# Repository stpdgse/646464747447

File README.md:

# Automated PCB toolchain

One script sets up a headless, scriptable PCB workflow on Ubuntu 24.04 (x86_64):

| Tool | Purpose |
|---|---|
| KiCad 9.0 (PCBNew, `kicad-cli`) | Board editor, DRC, Gerber/drill export, Python `pcbnew` API |
| SKiDl | Describe circuits in Python, emit KiCad netlists |
| Fabrication Toolkit (Benny Megidish) | JLCPCB-ready Gerber / BOM / CPL output |
| Freerouting | Headless autorouter (Specctra DSN in, SES out) |

## Install

```bash
sudo ./setup-eda.sh            # install everything, then run the smoke test
sudo ./setup-eda.sh --no-test  # install only
sudo ./setup-eda.sh --test     # smoke test only
```

The script is idempotent. Open a new shell afterwards (or `source /etc/profile.d/eda.sh`).

## Pipeline

```
SKiDl script ──► netlist ──► PCBNew (place, outline) ──► DSN ──► Freerouting ──► SES
                                                                                  │
                        JLCPCB files ◄── Fabrication Toolkit ◄── routed .kicad_pcb ◄┘
```

Route a board headless:

```bash
freerouting -de board.dsn -do board.ses --gui.enabled=false
```

## Gotchas this script already handles

- SKiDl defaults to KiCad 10 mode; scripts must call `set_default_tool(KICAD9)`.
- SKiDl needs `KICAD9_SYMBOL_DIR` and KiCad's global `fp-lib-table`, which KiCad only
  creates on first GUI launch. The script sets both up.
- SKiDl's dependencies fail to build with the distro's patched pip, so it lives in a venv
  (`/opt/eda/venv`) on the system Python 3.12, which is the interpreter `pcbnew` is built for.
- Freerouting 2.4.1 needs Java 25; the default Java 21 fails with `UnsupportedClassVersionError`.
- The Fabrication Toolkit download is verified against the SHA-256 published in KiCad's
  plugin index before it is installed.

## Game Boy Color-style handheld (practice board)

A beginner-solderable, all through-hole handheld: ESP32-S3-DevKitC-1 on the underside, a 2.8"
ILI9341 LCD, 8 buttons, an I2S amplifier module. Board v0.3 is 90 x 98 mm (inside JLCPCB's cheapest
size tier). Full requirements and every verified fact: `docs/gbc-handheld-spec.md`.
Build and soldering instructions: `gbc-handheld/ASSEMBLY.md`. Shopping list: `gbc-handheld/build/BOM.md`.

Rebuild everything from source (after `sudo ./setup-eda.sh`):

```bash
source /etc/profile.d/eda.sh
python3 gbc-handheld/schematic.py                                  # SKiDl -> netlist, ERC
python3 -I gbc-handheld/verify_netlist.py gbc-handheld/build/gbc_handheld.net
python3 gbc-handheld/build_board.py route                          # place, autoroute, fix thermals
python3 gbc-handheld/verify_board.py                               # board vs netlist, fab limits
kicad-cli pcb drc --severity-all --all-track-errors --output /tmp/drc.rpt gbc-handheld/build/gbc_handheld.kicad_pcb
python3 -I gbc-handheld/make_bom.py gbc-handheld/build/gbc_handheld.net
```

Or run every check, the fab export, BOM and all pictures in one go: `gbc-handheld/check_all.sh`
(audit results and what each check proves: `docs/gbc-handheld-spec.md`, section 15).

Nothing here has been tested on real hardware yet.

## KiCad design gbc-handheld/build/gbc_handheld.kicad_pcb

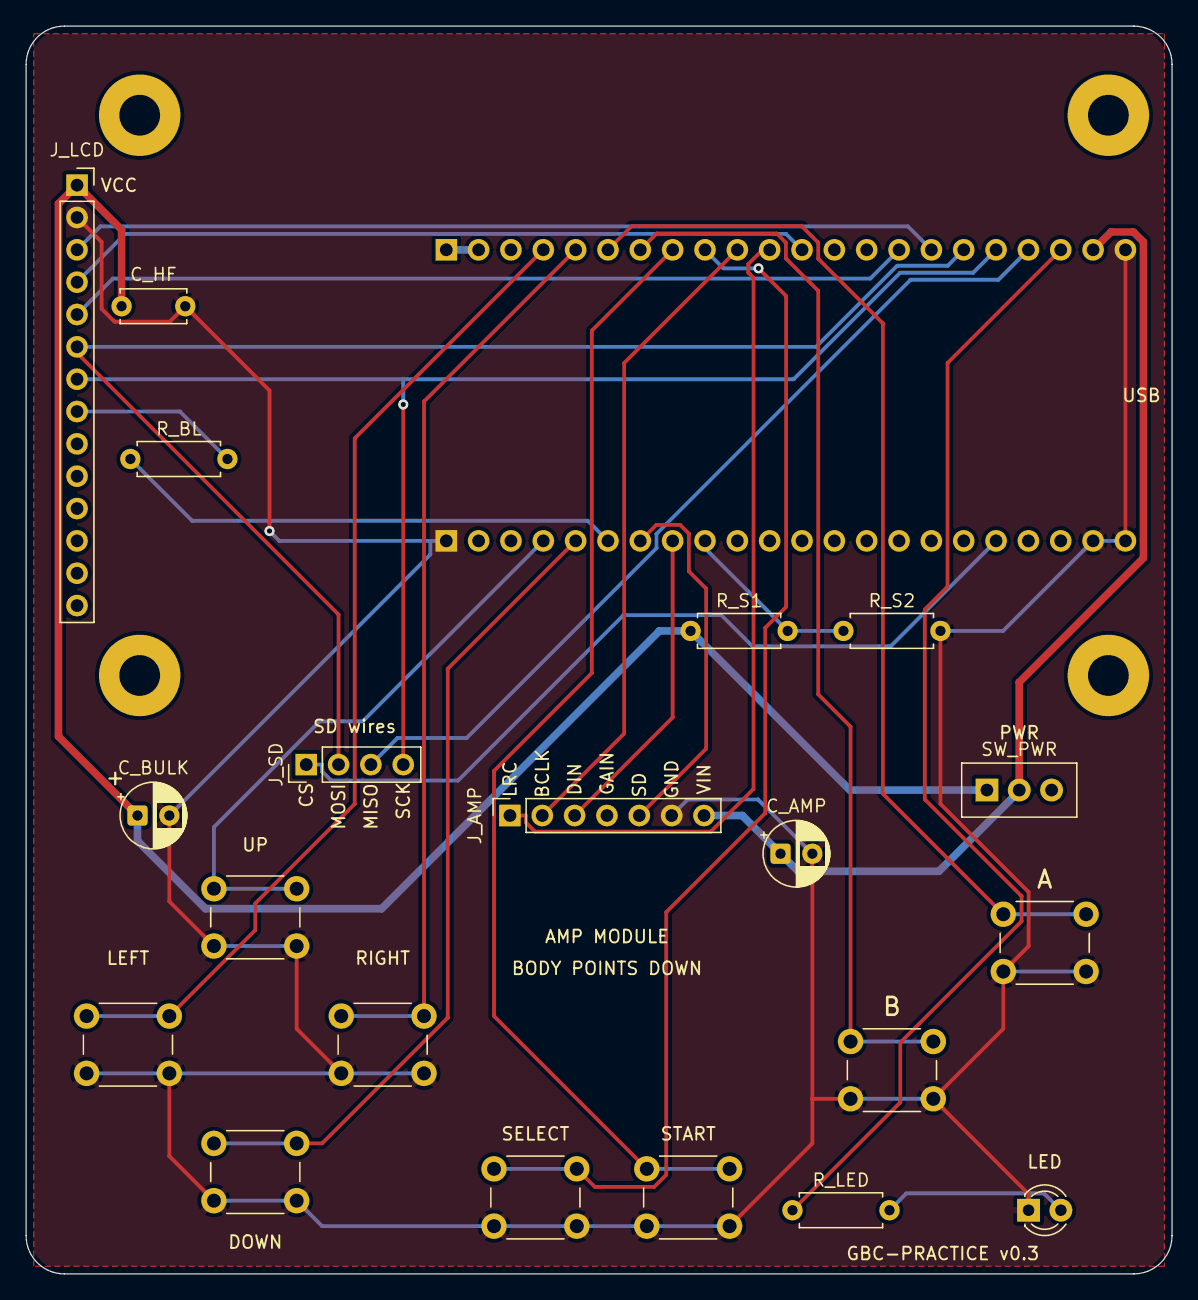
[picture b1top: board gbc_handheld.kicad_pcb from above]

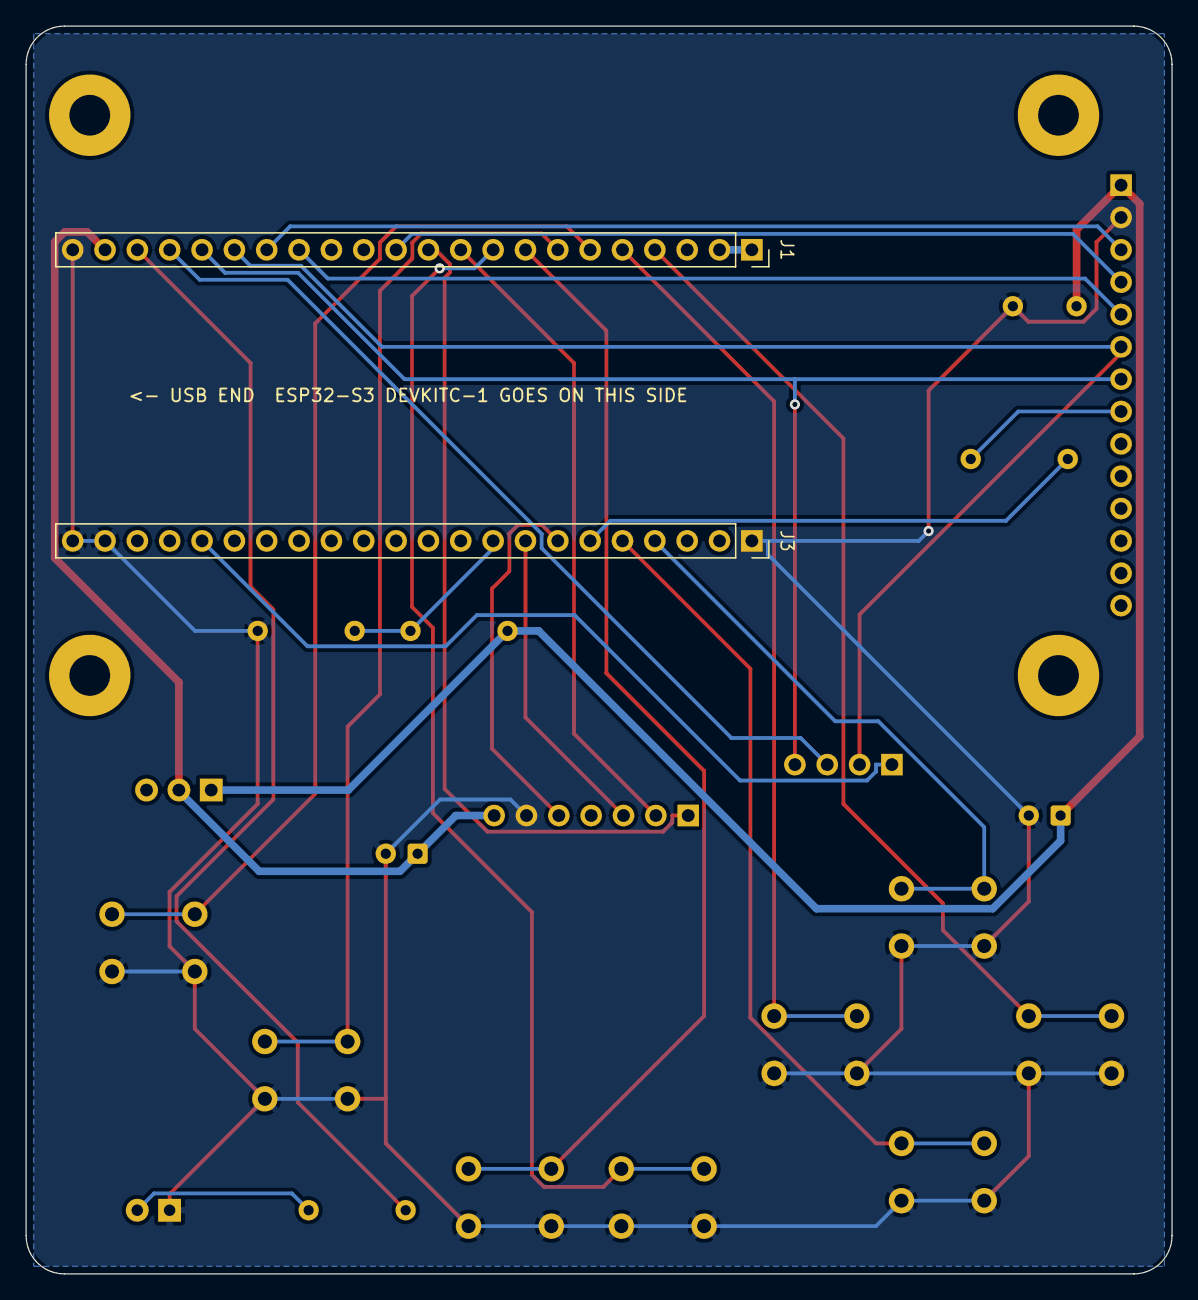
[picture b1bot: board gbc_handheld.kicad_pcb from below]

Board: 2 copper layers, 90.0 x 98.0 mm, 26 parts (2 on the bottom side), 28 nets.

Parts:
C_AMP: 100uF; CP_Radial_D5.0mm_P2.50mm
C_BULK: 100uF; CP_Radial_D5.0mm_P2.50mm
C_HF: 100nF; C_Disc_D5.0mm_W2.5mm_P5.00mm
D_STATUS: LED 3mm; LED_D3.0mm
H1, H2, H3, H4: MountingHole_3.2mm_M3_Pad
J1: ESP32-S3-DevKitC-1 J1; PinSocket_1x22_P2.54mm_Vertical
J3: ESP32-S3-DevKitC-1 J3; PinSocket_1x22_P2.54mm_Vertical
J_AMP: MAX98357A: LRC BCLK DIN GAIN SD GND VIN; PinSocket_1x07_P2.54mm_Vertical
J_LCD: 2.8in ILI9341 (MSP2807); PinSocket_1x14_P2.54mm_Vertical
J_SD: SD wires: CS MOSI MISO SCK; PinHeader_1x04_P2.54mm_Vertical
R_BL: 1k; R_Axial_DIN0207_L6.3mm_D2.5mm_P7.62mm_Horizontal
R_LED: 1k; R_Axial_DIN0207_L6.3mm_D2.5mm_P7.62mm_Horizontal
R_S1: 15k; R_Axial_DIN0207_L6.3mm_D2.5mm_P7.62mm_Horizontal
R_S2: 22k; R_Axial_DIN0207_L6.3mm_D2.5mm_P7.62mm_Horizontal
SW1: SW_UP; SW_PUSH_6mm
SW2: SW_DOWN; SW_PUSH_6mm
SW3: SW_LEFT; SW_PUSH_6mm
SW4: SW_RIGHT; SW_PUSH_6mm
SW5: SW_A; SW_PUSH_6mm
SW6: SW_B; SW_PUSH_6mm
SW7: SW_START; SW_PUSH_6mm
SW8: SW_SELECT; SW_PUSH_6mm
SW_PWR: Power (slide); SW_Slide_SS12D00G3

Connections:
+3V3: J1.1, J1.2
+5V_SW: C_BULK.1, C_HF.1, J_LCD.1, R_S1.1, SW_PWR.1
+5V_USB: C_AMP.1, J1.21, J_AMP.7, SW_PWR.2
AUDIO_BCLK: J1.10, J_AMP.2
AUDIO_DIN: J3.8, J_AMP.3
AUDIO_LRC: J1.11, J_AMP.1
AUDIO_SD: J3.7, J_AMP.5
BTN_A: J1.6, SW5.1
BTN_B: J1.7, SW6.1
BTN_DOWN: J3.5, SW2.1
BTN_LEFT: J1.4, SW3.1
BTN_RIGHT: J1.5, SW4.1
BTN_SELECT: J1.9, SW8.1
BTN_START: J1.8, SW7.1
BTN_UP: J3.4, SW1.1
GND: C_AMP.2, C_BULK.2, C_HF.2, D_STATUS.1, J1.22, J3.1, J3.21, J3.22, J_AMP.6, J_LCD.2, R_S2.2, SW1.2, SW2.2, SW3.2, SW4.2, SW5.2, SW6.2, SW7.2, SW8.2
LCD_BL: J3.6, R_BL.1
LCD_CS: J1.16, J_LCD.3
LCD_DC: J1.15, J_LCD.5
LCD_RST: J1.12, J_LCD.4
unnamed: J_LCD.8, R_BL.2
unnamed: D_STATUS.2, R_LED.2
PWR_SENSE: J3.9, R_S1.2, R_S2.1
SD_CS: J3.18, J_SD.1
SPI_MISO: J1.19, J_SD.3
SPI_MOSI: J1.17, J_LCD.6, J_SD.2
SPI_SCK: J1.18, J_LCD.7, J_SD.4
STATUS_LED: J1.20, R_LED.1
